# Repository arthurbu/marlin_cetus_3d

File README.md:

# Marlin 3D Printer Firmware - Cetus3D Mod

Additional documentation can be found at the [Marlin Home Page](http://marlinfw.org/).
Please test this firmware and let us know if it misbehaves in any way. Volunteers are standing by!

## Marlin 2.0 Bugfix Branch

__Not for production use. Use with caution!__

Marlin 2.0 takes this popular RepRap firmware to the next level with support for much faster 32-bit processor boards.

This branch is for patches to the latest 2.0.x release version. Periodically this branch will form the basis for the next minor 2.0.x release.

Download earlier versions of Marlin on the [Releases page](https://github.com/MarlinFirmware/Marlin/releases).

## Building Marlin 2.0

To build Marlin 2.0 you'll need [Arduino IDE 1.9](https://www.arduino.cc/en/main/software) or [PlatformIO](http://docs.platformio.org/en/latest/ide.html#platformio-ide). We've posted detailed instructions on how to [build Marlin 2.0 for ARM](http://marlinfw.org/docs/basics/install_arm.html).

## Hardware Abstraction Layer (HAL)

Marlin 2.0 adds a new abstraction layer so that Marlin can build and run on 32-bit boards while still retaining full 8-bit AVR compatibility. In this way, features can be enhanced for more powerful platforms while still supporting AVR, whereas splitting up the code would make it harder to maintain and keep everything in sync.

### Current HALs

  name|processor|speed|flash|sram|logic|fpu
  ----|---------|-----|-----|----|-----|---
  [Arduino AVR](https://www.arduino.cc/)|ATmega, ATTiny, etc.|16-20MHz|64-256k|2-8k|5V|no
  [Teensy++ 2.0](http://www.microchip.com/wwwproducts/en/AT90USB1286)|[AT90USB1286](http://www.microchip.com/wwwproducts/en/AT90USB1286)|16MHz|128k|8k|5V|no
  [Due](https://www.arduino.cc/en/Guide/ArduinoDue), [RAMPS-FD](http://www.reprap.org/wiki/RAMPS-FD), etc.|[SAM3X8E ARM-Cortex M3](http://www.microchip.com/wwwproducts/en/ATsam3x8e)|84MHz|512k|64+32k|3.3V|no
  [Re-ARM](https://www.kickstarter.com/projects/1245051645/re-arm-for-ramps-simple-32-bit-upgrade)|[LPC1768 ARM-Cortex M3](http://www.nxp.com/products/microcontrollers-and-processors/arm-based-processors-and-mcus/lpc-cortex-m-mcus/lpc1700-cortex-m3/512kb-flash-64kb-sram-ethernet-usb-lqfp100-package:LPC1768FBD100)|100MHz|512k|32+16+16k|3.3-5V|no
  [MKS SBASE](http://forums.reprap.org/read.php?13,499322)|LPC1768 ARM-Cortex M3|100MHz|512k|32+16+16k|3.3-5V|no
  [Azteeg X5 GT](https://www.panucatt.com/azteeg_X5_GT_reprap_3d_printer_controller_p/ax5gt.htm)|LPC1769 ARM-Cortex M3|120MHz|512k|32+16+16k|3.3-5V|no
  [Selena Compact](https://github.com/Ales2-k/Selena)|LPC1768 ARM-Cortex M3|100MHz|512k|32+16+16k|3.3-5V|no
  [Teensy 3.5](https://www.pjrc.com/store/teensy35.html)|ARM-Cortex M4|120MHz|512k|192k|3.3-5V|yes
  [Teensy 3.6](https://www.pjrc.com/store/teensy36.html)|ARM-Cortex M4|180MHz|1M|256k|3.3V|yes

### HALs in Development

  name|processor|speed|flash|sram|logic|fpu
  ----|---------|-----|-----|----|-----|---
  [STEVAL-3DP001V1](http://www.st.com/en/evaluation-tools/steval-3dp001v1.html)|[STM32F401VE Arm-Cortex M4](http://www.st.com/en/microcontrollers/stm32f401ve.html)|84MHz|512k|64+32k|3.3-5V|yes
  [Smoothieboard](http://reprap.org/wiki/Smoothieboard)|LPC1769 ARM-Cortex M3|120MHz|512k|64k|3.3-5V|no

## Submitting Patches

Proposed patches should be submitted as a Pull Request against the ([bugfix-2.0.x](https://github.com/MarlinFirmware/Marlin/tree/bugfix-2.0.x)) branch.

- This branch is for fixing bugs and integrating any new features for the duration of the Marlin 2.0.x life-cycle.
- Follow the [Coding Standards](http://marlinfw.org/docs/development/coding_standards.html) to gain points with the maintainers.
- Please submit your questions and concerns to the [Issue Queue](https://github.com/MarlinFirmware/Marlin/issues).

### [RepRap.org Wiki Page](http://reprap.org/wiki/Marlin)

## Credits

The current Marlin dev team consists of:
 - Roxanne Neufeld [[@Roxy-3D](https://github.com/Roxy-3D)] - English
 - Scott Lahteine [[@thinkyhead](https://github.com/thinkyhead)] - English
 - Bob Kuhn [[@Bob-the-Kuhn](https://github.com/Bob-the-Kuhn)] - English
 - Chris Pepper [[@p3p](https://github.com/p3p)] - English
 - João Brazio [[@jbrazio](https://github.com/jbrazio)] - Portuguese, English

## License

Marlin is published under the [GPL license](/LICENSE) because we believe in open development. The GPL comes with both rights and obligations. Whether you use Marlin firmware as the driver for your open or closed-source product, you must keep Marlin open, and you must provide your compatible Marlin source code to end users upon request. The most straightforward way to comply with the Marlin license is to make a fork of Marlin on Github, perform your modifications, and direct users to your modified fork.

While we can't prevent the use of this code in products (3D printers, CNC, etc.) that are closed source or crippled by a patent, we would prefer that you choose another firmware or, better yet, make your own.

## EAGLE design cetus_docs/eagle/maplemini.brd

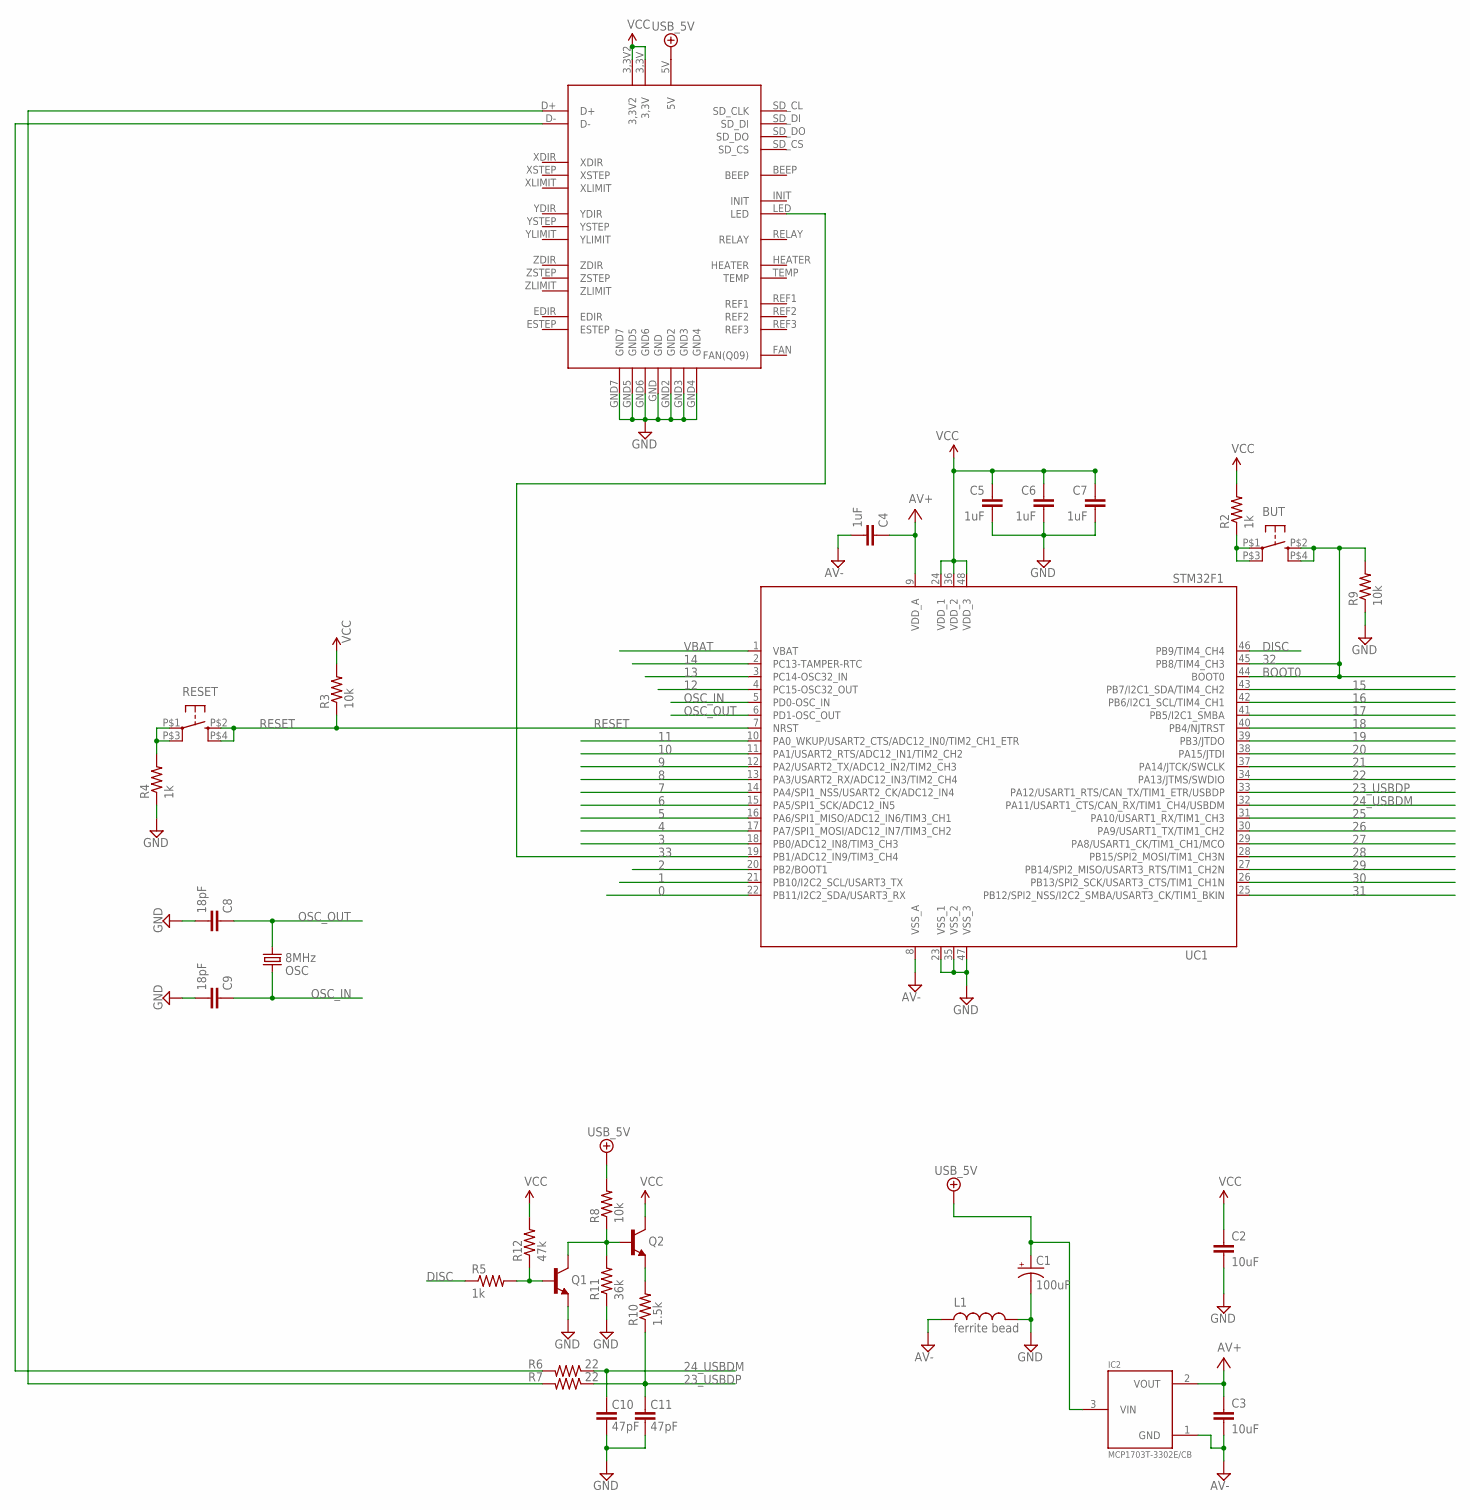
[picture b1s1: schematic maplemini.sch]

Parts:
BUT: KMR211GLFS; PUSHBUTTON-KMR241GLFS
C1: 100uF; EIA3216
C2, C3: 10uF; 0805
C4, C5, C6, C7: 1uF; C0402
C8, C9: 18pF; C0402
C10, C11: 47pF; C0402
IC2: MCP1703T-3302E/CB; SOT23
L1: ferrite bead; 0603
OSC: 8MHz; CRYSTAL-SMD-5X3
Q1, Q2: NPN-BJT; SOT23
R2, R4, R5: 1k; C0402
R3, R8, R9: 10k; C0402
R6, R7: 22; C0402
R10: 1.5k; C0402
R11: 36k; C0402
R12: 47k; C0402
RESET: KMR211GLFS; PUSHBUTTON-KMR241GLFS
U$1: CETUS_CONTROLLER
UC1: STM32F1; LQFP48

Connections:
0: UC1.22 (PB11/I2C2_SDA/USART3_RX)
1: UC1.21 (PB10/I2C2_SCL/USART3_TX)
2: UC1.20 (PB2/BOOT1)
3: UC1.18 (PB0/ADC12_IN8/TIM3_CH3)
4: UC1.17 (PA7/SPI1_MOSI/ADC12_IN7/TIM3_CH2)
5: UC1.16 (PA6/SPI1_MISO/ADC12_IN6/TIM3_CH1)
6: UC1.15 (PA5/SPI1_SCK/ADC12_IN5)
7: UC1.14 (PA4/SPI1_NSS/USART2_CK/ADC12_IN4)
8: UC1.13 (PA3/USART2_RX/ADC12_IN3/TIM2_CH4)
9: UC1.12 (PA2/USART2_TX/ADC12_IN2/TIM2_CH3)
10: UC1.11 (PA1/USART2_RTS/ADC12_IN1/TIM2_CH2)
11: UC1.10 (PA0_WKUP/USART2_CTS/ADC12_IN0/TIM2_CH1_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)
12: UC1.4 (PC15-OSC32_OUT)
13: UC1.3 (PC14-OSC32_IN)
14: UC1.2 (PC13-TAMPER-RTC)
15: UC1.43 (PB7/I2C1_SDA/TIM4_CH2)
16: UC1.42 (PB6/I2C1_SCL/TIM4_CH1)
17: UC1.41 (PB5/I2C1_SMBA)
18: UC1.40 (PB4/NJTRST)
19: UC1.39 (PB3/JTDO)
20: UC1.38 (PA15/JTDI)
21: UC1.37 (PA14/JTCK/SWCLK)
22: UC1.34 (PA13/JTMS/SWDIO)
23_USBDP: C11.2, R7.1, R10.1, UC1.33 (PA12/USART1_RTS/CAN_TX/TIM1_ETR/USBDP)
24_USBDM: C10.2, R6.1, UC1.32 (PA11/USART1_CTS/CAN_RX/TIM1_CH4/USBDM)
25: UC1.31 (PA10/USART1_RX/TIM1_CH3)
26: UC1.30 (PA9/USART1_TX/TIM1_CH2)
27: UC1.29 (PA8/USART1_CK/TIM1_CH1/MCO)
28: UC1.28 (PB15/SPI2_MOSI/TIM1_CH3N)
29: UC1.27 (PB14/SPI2_MISO/USART3_RTS/TIM1_CH2N)
30: UC1.26 (PB13/SPI2_SCK/USART3_CTS/TIM1_CH1N)
31: UC1.25 (PB12/SPI2_NSS/I2C2_SMBA/USART3_CK/TIM1_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)
32: BUT.P$2 (2), BUT.P$4 (4), R9.2, UC1.44 (BOOT0), UC1.45 (PB8/TIM4_CH3)
33: U$1.LED, UC1.19 (PB1/ADC12_IN9/TIM3_CH4)
+5V/2: C1.A (+), IC2.3 (VIN), R8.2, U$1.5V
AV+: C3.1, C4.1, IC2.2 (VOUT), UC1.9 (VDD_A)
AV-: C3.2, C4.2, IC2.1 (GND), L1.1, UC1.8 (VSS_A)
DGND: C1.C (-), C2.2, C5.2, C6.2, C7.2, C8.2, C9.2, C10.1, C11.1, L1.2, Q1.2 (E), R4.1, R9.1, R11.1, UC1.23 (VSS_1), UC1.35 (VSS_2), UC1.47 (VSS_3)
DISC: R5.1, UC1.46 (PB9/TIM4_CH4)
GND: U$1.GND, U$1.GND2, U$1.GND3, U$1.GND4, U$1.GND5, U$1.GND6, U$1.GND7
unnamed: BUT.P$1 (1), BUT.P$3 (3), R2.1
unnamed: R4.2, RESET.P$1 (1), RESET.P$3 (3)
unnamed: Q2.2 (E), R10.2
unnamed: R6.2, U$1.D-
unnamed: R7.2, U$1.D+
unnamed: Q1.3 (C), Q2.1 (B), R8.1, R11.2
unnamed: Q1.1 (B), R5.2, R12.1
OSC_IN: C9.1, OSC.3 (2), UC1.5 (PD0-OSC_IN)
OSC_OUT: C8.1, OSC.1, UC1.6 (PD1-OSC_OUT)
RESET: R3.1, RESET.P$2 (2), RESET.P$4 (4), UC1.7 (NRST)
VBAT: UC1.1 (VBAT)
VCC: C2.1, C5.1, C6.1, C7.1, Q2.3 (C), R2.2, R3.2, R12.2, U$1.3,3V, U$1.3,3V2, UC1.24 (VDD_1), UC1.36 (VDD_2), UC1.48 (VDD_3)

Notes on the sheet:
BOOT0

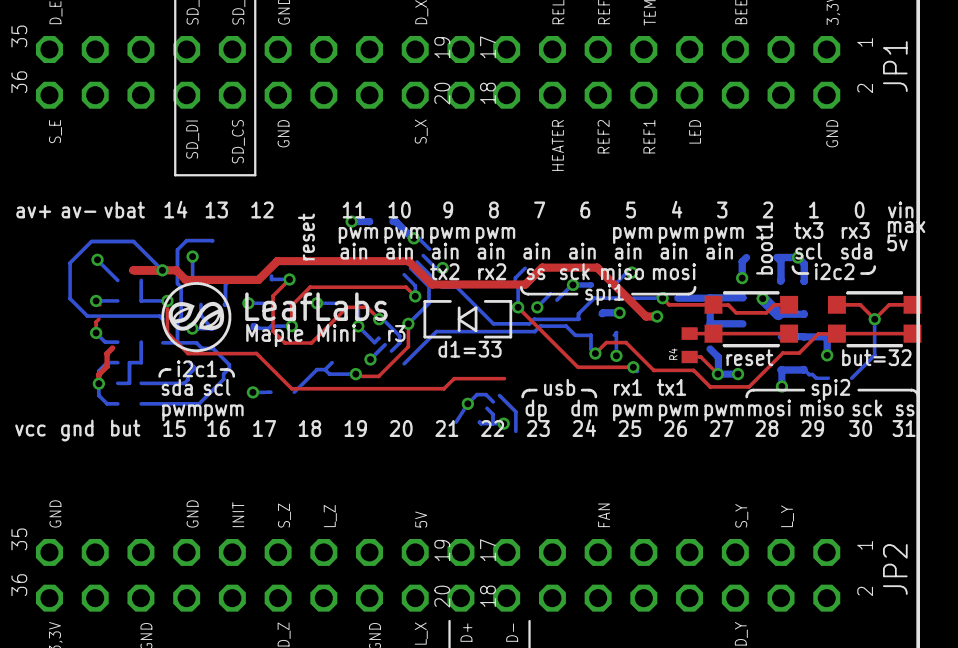
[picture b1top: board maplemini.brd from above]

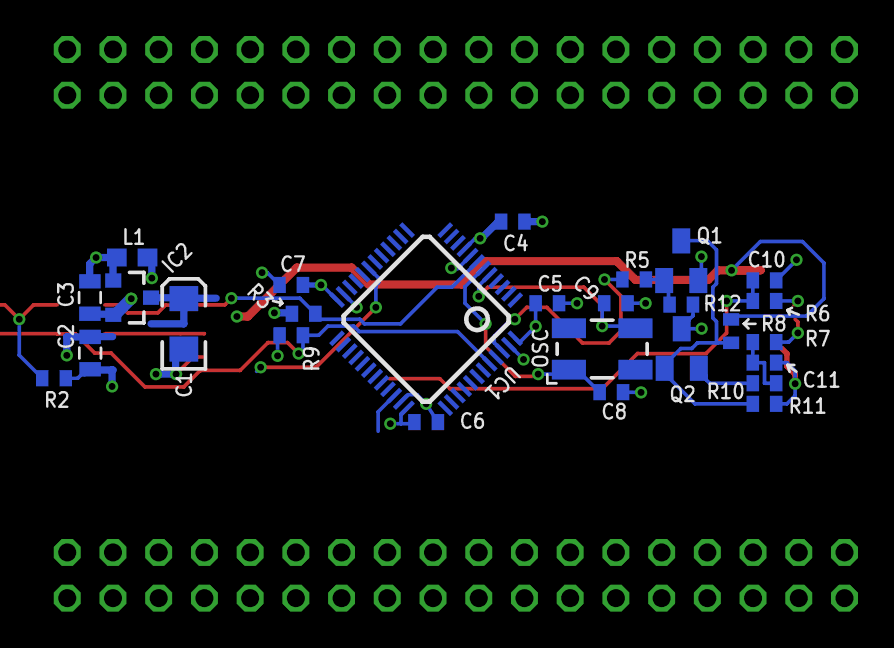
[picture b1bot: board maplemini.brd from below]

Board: 2 copper layers, 31 parts (27 on the bottom side), 21 nets.

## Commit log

2018-05-11 Some docs
2018-05-12 DFU Uploader
2018-05-12 Thermistor profile
2018-05-12 General configuration
2018-05-12 Modified README
2018-05-12 Missing BOARD_CETUS3D and pins definitions
2018-05-13 Eagle projects
2018-05-15 codeblocks project and build tools
2018-05-15 configs and dirty hacks merged from develop branch
2018-05-16 fixed CodeBlocks build script
2018-05-16 systick hack moved from stm32duino core to Marlin
2018-05-20 temperature routing uses systick interrupt
2018-05-23 testing bltouch
2018-05-26 fixes after updating to latest marlin
2018-05-26 updated feedrates
2018-05-27 bltouch - more testing
2018-06-01 issue introduced by last merge
2018-06-01 servo timing fixed
2018-06-01 BLtouch tuning
2018-06-01 feedrates increased
2018-06-10 missing __disable_irq, __enable_irq
2018-06-10 quick homing support
2018-06-23 .check_possible_change() chaged to .update()
2018-06-24 detach interrupts right after detecting home position
2018-06-24 endstop isr skip if not homing
